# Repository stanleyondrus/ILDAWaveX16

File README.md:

# ILDAWaveX16 - Open Source Laser DAC

**ILDAWaveX16** is an open-source, high-resolution, wireless laser DAC with SD-card playback, network control, and ILDA output.

Traditional laser DACs are often expensive, proprietary, or limited in flexibility, especially for those who want to experiment with laser systems, build custom projectors, or interface with low-cost driver kits.

The goal of this project is to create the "Arduino of laser DACs" - a flexible, hackable platform for makers and enthusiasts that can serve as a foundation for any DIY laser project, capable of real show control, yet simple enough for beginners and hobbyists to learn from.

Full documentation is available at [stanleyprojects.com](https://stanleyprojects.com/projects/ildawavex16)

## Features
- **ESP32-S3 dual-core MCU** @ 240 MHz with native USB, Wi-Fi, and BLE  
- **16-bit, 8-channel DAC (DAC80508)**  
  - X/Y resolution: 65,536 x 65,536  
  - R/G/B resolution: 281 trillion colors  
  - Intensity resolution: 65,536  
  - 16-bit user-programmable channels USR1/USR2  
- **ILDA DB25 connector** for standard projectors  
- **JST XH connectors** for direct wiring to driver kits
- **USB-C power** (no need for bipolar PSU) or optional ±15V external supply  
- **microSD card slot** for ILDA file playback  
- Compact: 55 x 53 mm  

## Firmware

This repository provides a **starting-point firmware**, which is **open-source** and built on the **Arduino framework**. It serves as a foundation for experimenting, learning, and customizing the board for your own projects.  

Although still in development and likely to contain bugs, it includes basic implementations of:
- Playing `.ild` files directly from the SD card  
- **IDN (ILDA Digital Network)** - standard real-time streaming
- **IWP (ILDAWaveProtocol)** - simple, lightweight UDP streaming
- **Web server interface** to control SD card playback, brightness, scan speed, and Wi-Fi settings

Contributions are welcome! Feel free to share improvements, optimizations, or custom firmware to help the community.

## Repository Contents
- `pcb/` - Schematic, BOM  
- `firmware/ILDAWaveX16` - ESP32-S3 source code (Arduino / PlatformIO)  
- `firmware/Python/iwp-ilda.py` - Python script to open `.ild` files and stream over UDP using IWP  
- `firmware/Python/iwp-gen.ipynb` - Jupyter notebook for generating patterns and streaming them via IWP

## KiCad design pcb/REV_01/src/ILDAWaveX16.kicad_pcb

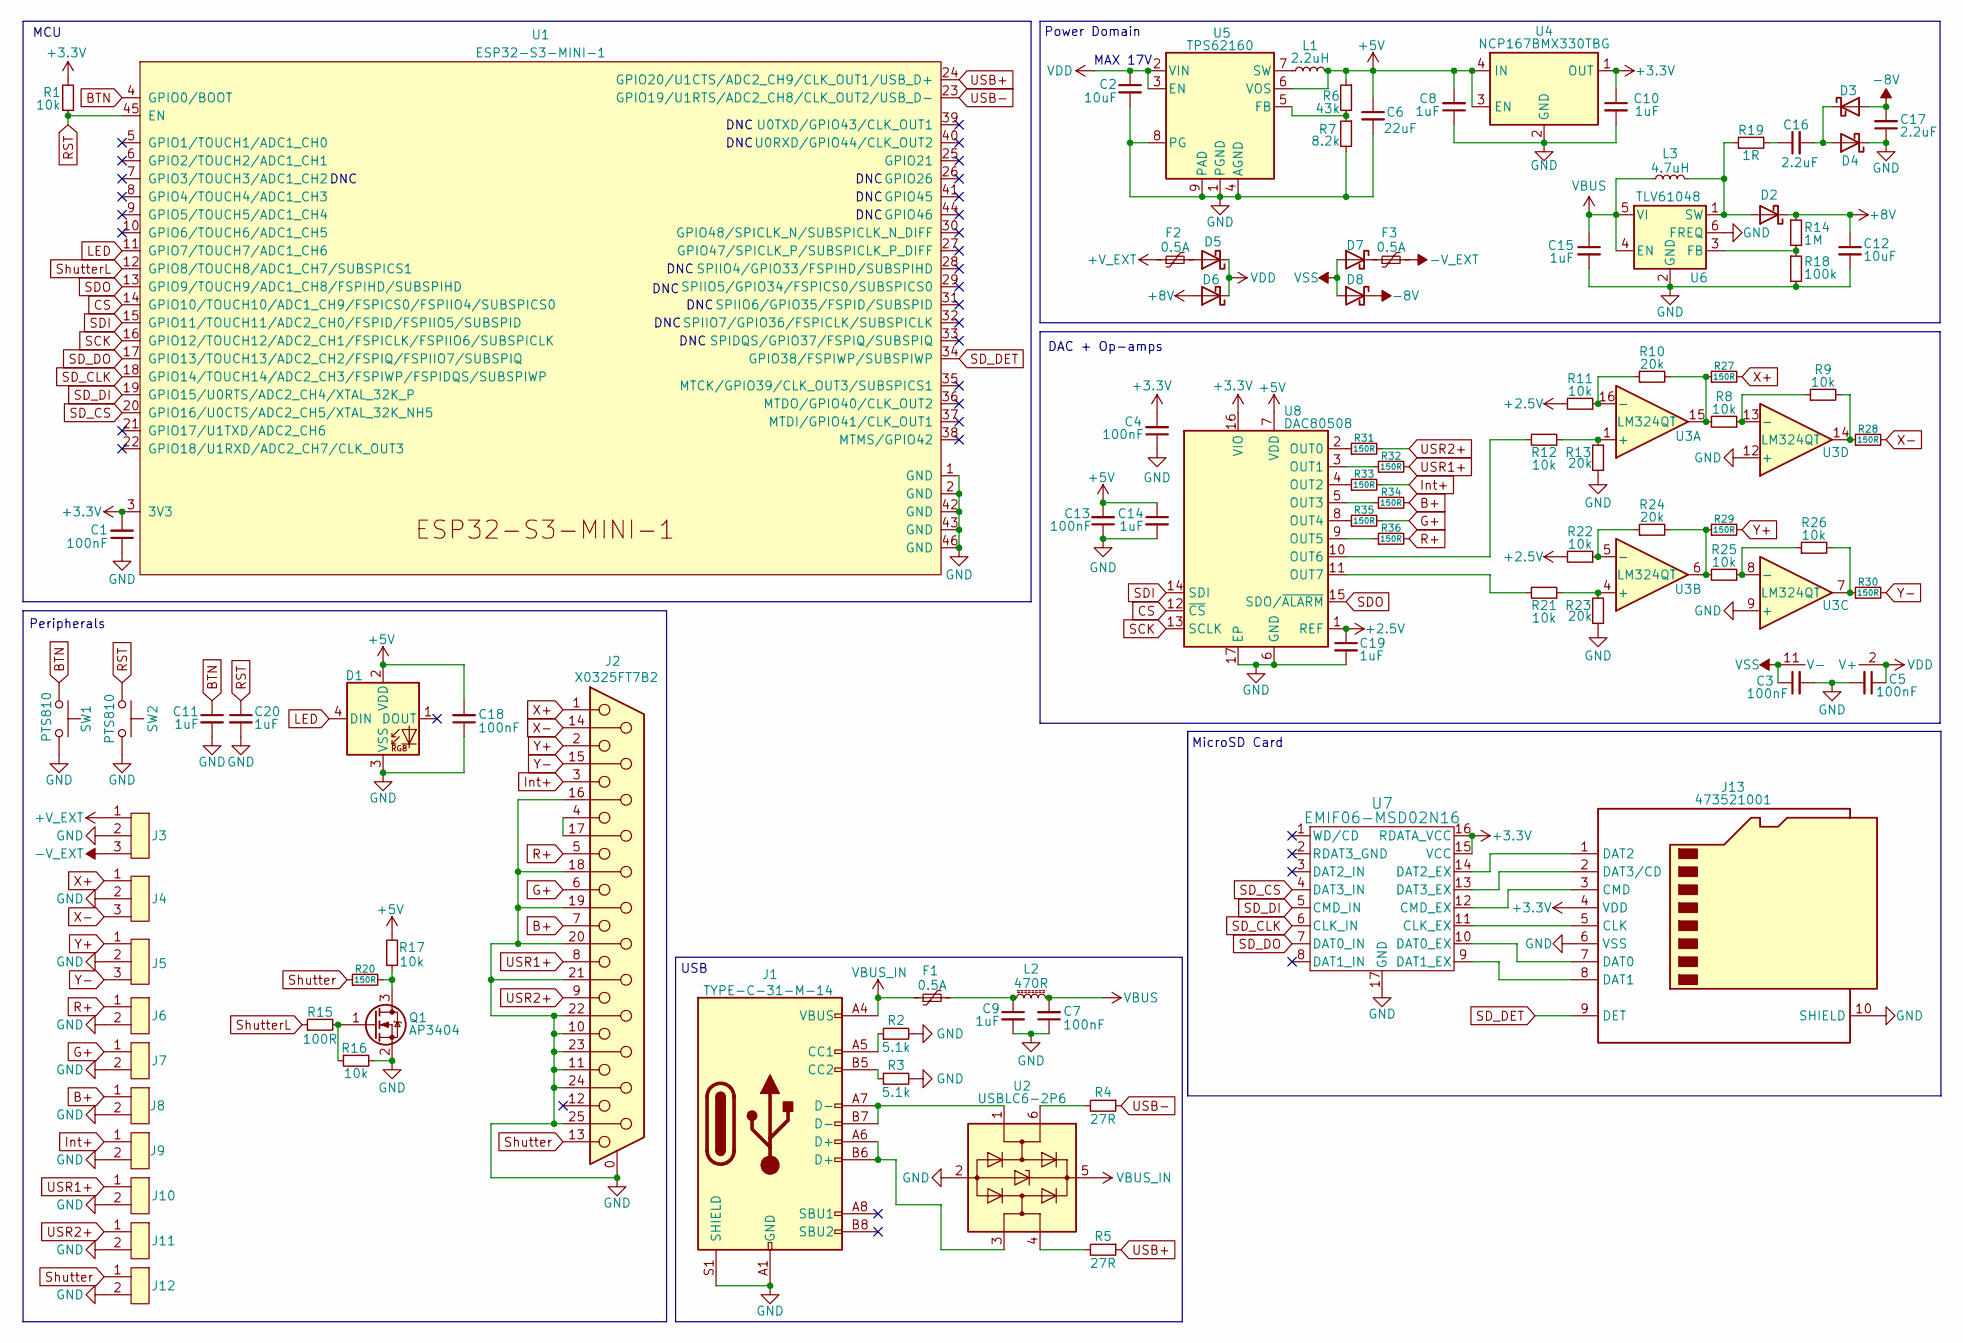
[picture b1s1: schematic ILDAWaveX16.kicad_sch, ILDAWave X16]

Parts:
C1, C3, C4, C5, C7, C13, C18: 100nF; C_0402_1005Metric; MPN CC0402KRX7R7BB104; LCSC# C60474
C2: 10uF; C_0805_2012Metric; MPN CL21A106KAYNNNE; LCSC# C15850
C6: 22uF; C_0805_2012Metric; MPN CL21A226MQQNNNF; LCSC# C307531
C8, C9, C10, C11, C14, C15, C19, C20: 1uF; C_0402_1005Metric; MPN CL05A105KA5NQNC; LCSC# C52923
C12: 10uF; C_1210_3225Metric; MPN CC1206KKX5R8BB106; LCSC# C128855
C16, C17: 2.2uF; C_0603_1608Metric; MPN GRM188R61H225KE11D; LCSC# C162273
D1: XL-1010RGBC-WS2812B; MPN XL-1010RGBC-WS2812B; LCSC# C5349953
D2, D3, D4, D5, D6, D7, D8: 1N5819W; D_SOD-123; MPN 1N5819W; LCSC# C2905650
F1, F2, F3: 0.5A; Fuse_0805_2012Metric; MPN SMD0805-050-16V; LCSC# C2833485
J1: TYPE-C-31-M-14; USB_C_Receptacle_HRO_TYPE-C-31-M-14; MPN TYPE-C-31-M-14; LCSC# C223907
J2: X0325FT7B2; J_DB25_Female_X0325FT7B2; MPN X0325FT7B2; LCSC# C7464461
J3, J4, J5: J_JST-XH-B3B; JST_XH_B3B-XH-A_1x03_P2.50mm_Vertical; MPN B3B-XH-A(LF)(SN); LCSC# C144394
J6, J7, J8, J9, J10, J11, J12: J_JST-XH-B2B; JST_XH_B2B-XH-A_1x02_P2.50mm_Vertical; MPN B2B-XH-A(LF)(SN); LCSC# C158012
J13: 473521001; microSD_HC_Molex_47352-1001; MPN 473521001; LCSC# C293569
L1: 2.2uH; VLCF4020; MPN VLCF4020T-2R2N1R7; LCSC# C136245
L2: 470R; L_0603_1608Metric; MPN MPZ1608B471ATA00; LCSC# C114780
L3: 4.7uH; L_Coilcraft_XAL4030-XXX; MPN XAL4030-472; LCSC# C19191688
Q1: AP3404; SOT-23; MPN AP3404; LCSC# C2842665
R1, R8, R9, R11, R12, R16, R17, R21, R22, R25, R26: 10k; R_0402_1005Metric; MPN RC0402FR-7W10KL; LCSC# C851848
R2, R3: 5.1k; R_0402_1005Metric; MPN AC0402FR-075K1L; LCSC# C144745
R4, R5: 27R; R_0402_1005Metric; MPN RC0402JR-0727RL; LCSC# C137890
R6: 43k; R_0402_1005Metric; MPN RC0402FR-0743KL; LCSC# C185415
R7: 8.2k; R_0402_1005Metric; MPN RC0402FR-078K2L; LCSC# C137929
R10, R13, R23, R24: 20k; R_0402_1005Metric; MPN RC0402FR-0720KL; LCSC# C93942
R14: 1M; R_0402_1005Metric; MPN RK73G1ETTP1004F; LCSC# C516088
R15: 100R; R_0402_1005Metric; MPN AC0402FR-07100RL; LCSC# C144808
R18: 100k; R_0402_1005Metric; MPN 0402WGF1003TCE; LCSC# C25741
R19: 1R; R_0603_1608Metric; MPN HP03W5F100KT5E; LCSC# C2759448
R20, R27, R28, R29, R30, R31, R32, R33, R34, R35, R36: 150R; R_0402_1005Metric; MPN AC0402FR-07150RL; LCSC# C226790
SW1, SW2: PTS810; SW_CK_PTS810; MPN PTS810SJG250SMTRLFS; LCSC# C221895
U1: ESP32-S3-MINI-1; MPN ESP32-S3-MINI-1; LCSC# C2913206
U2: USBLC6-2P6; SOT-666; MPN USBLC6-2P6; LCSC# C15999
U3: LM324QT; QFN-16-1EP_3x3mm_P0.5mm_EP1.7x1.7mm; MPN LM324QT; LCSC# C183029
U4: NCP167BMX330TBG; XDFN-4; MPN NCP167BMX330TBG; LCSC# C892227
U5: TPS62160; WSON-8-1EP_2x2mm_P0.5mm_EP0.9x1.6mm_ThermalVias; MPN TPS62160DSG; LCSC# C324077
U6: TLV61048; SOT-23-6; MPN TLV61048DBV; LCSC# C2861467
U7: EMIF06-MSD02N16; MICROQFN16_1P25X3P55X0P4_STM; MPN EMIF06-MSD02N16; LCSC# C5267594
U8: DAC80508; Texas_RTE0016D_WQFN-16-1EP_3x3mm_P0.5mm_EP0.8x0.8mm_Thermal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; MPN DAC80508MRTE; LCSC# C2679529

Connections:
+2.5V: C19.1, R11.2, R22.2, U8.1 (REF)
+3.3V: C1.2, C4.2, C10.1, J13.4 (VDD), R1.2, U1.3 (3V3), U4.1 (OUT), U7.15 (VCC), U7.16 (RDATA_VCC), U8.16 (VIO)
+5V: C6.1, C8.2, C13.2, C14.1, C18.2, D1.2 (VDD), L1.2, R6.1, R17.2, U4.3 (EN), U4.4 (IN), U5.6 (VOS), U8.7 (VDD)
+8V: C12.1, D2.1 (K), D6.2 (A), R14.1
+V_EXT: F2.1, J3.1
-8V: C17.2, D3.2 (A), D8.1 (K)
-V_EXT: F3.2, J3.3
B+: J2.7, J8.1, R34.2
BTN: C11.1, SW1.1, SW1.2, U1.4 (GPIO0/BOOT)
CS: U1.14 (GPIO10/TOUCH10/ADC1_CH9/FSPICS0/FSPIIO4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), U8.12 (~CS)
G+: J2.6, J7.1, R35.2
GND: C1.1, C2.2, C3.2, C4.1, C5.2, C6.2, C7.1, C8.1, C9.2, C10.2, C11.2, C12.2, C13.1, C14.2, C15.2, C17.1, C18.1, C19.2, C20.2, D1.3 (VSS), D4.1 (K), J1.A1 (GND), J1.A12 (GND), J1.B1 (GND), J1.B12 (GND), J1.S1 (SHIELD), J2.0 (PAD), J2.10, J2.11, J2.16, J2.18, J2.19, J2.20, J2.21, J2.22, J2.23, J2.24, J2.25, J3.2, J4.2, J5.2, J6.2, J7.2, J8.2, J9.2, J10.2, J11.2, J12.2, J13.6 (VSS), J13.10 (SHIELD), Q1.2 (S), R2.2, R3.2, R7.2, R13.1, R16.2, R18.2, R23.1, SW1.3, SW1.4, SW2.3, SW2.4, U1.1 (GND), U1.2 (GND), U1.42 (GND), U1.43 (GND), U1.46 (GND), U2.2 (GND), U3.9 (+), U3.12 (+), U4.2 (GND), U4.5 (GND), U5.1 (PGND), U5.4 (AGND), U5.8 (PG), U5.9 (PAD), U6.2 (GND), U6.6 (FREQ), U7.17 (GND), U8.6 (GND), U8.17 (EP)
Int+: J2.3, J9.1, R33.2
LED: D1.4 (DIN), U1.11 (GPIO7/TOUCH7/ADC1_CH6)
unnamed: C9.1, F1.2, L2.1
unnamed: C16.1, R19.2
unnamed: D2.2 (A), L3.1, R19.1, U6.1 (SW)
unnamed: C16.2, D3.1 (K), D4.2 (A)
unnamed: D5.2 (A), F2.2
unnamed: D7.1 (K), F3.1
unnamed: J1.A5 (CC1), R2.1
unnamed: J1.B5 (CC2), R3.1
unnamed: J1.A6 (D+), J1.B6 (D+), U2.3 (I/O2)
unnamed: J1.A7 (D-), J1.B7 (D-), U2.1 (I/O1)
unnamed: J2.4, J2.17
unnamed: J13.5 (CLK), U7.11 (CLK_EX)
unnamed: J13.3 (CMD), U7.12 (CMD_EX)
unnamed: J13.7 (DAT0), U7.10 (DAT0_EX)
unnamed: J13.8 (DAT1), U7.9 (DAT1_EX)
unnamed: J13.1 (DAT2), U7.14 (DAT2_EX)
unnamed: J13.2 (DAT3/CD), U7.13 (DAT3_EX)
unnamed: Q1.3 (D), R17.1, R20.2
unnamed: Q1.1 (G), R15.2, R16.1
unnamed: R4.2, U2.6 (I/O1)
unnamed: R5.2, U2.4 (I/O2)
unnamed: R8.2, R10.2, R27.1, U3.15
unnamed: R24.2, R25.2, R29.1, U3.6
unnamed: R26.2, R30.1, U3.7
unnamed: R9.2, R28.1, U3.14
unnamed: R12.1, R13.2, U3.1 (+)
unnamed: R10.1, R11.1, U3.16 (-)
unnamed: R21.1, R23.2, U3.4 (+)
unnamed: R22.1, R24.1, U3.5 (-)
unnamed: R25.1, R26.1, U3.8 (-)
unnamed: R8.1, R9.1, U3.13 (-)
unnamed: R6.2, R7.1, U5.5 (FB)
unnamed: L1.1, U5.7 (SW)
unnamed: R14.2, R18.1, U6.3 (FB)
unnamed: R31.1, U8.2 (OUT0)
unnamed: R32.1, U8.3 (OUT1)
unnamed: R33.1, U8.4 (OUT2)
unnamed: R34.1, U8.5 (OUT3)
unnamed: R35.1, U8.8 (OUT4)
unnamed: R36.1, U8.9 (OUT5)
unnamed: R12.2, U8.10 (OUT6)
unnamed: R21.2, U8.11 (OUT7)
R+: J2.5, J6.1, R36.2
RST: C20.1, R1.1, SW2.1, SW2.2, U1.45 (EN)
SCK: U1.16 (GPIO12/TOUCH12/ADC2_CH1/FSPICLK/FSPIIO6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), U8.13 (SCLK)
SDI: U1.15 (GPIO11/TOUCH11/ADC2_CH0/FSPID/FSPIIO5/S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), U8.14 (SDI)
SDO: U1.13 (GPIO9/TOUCH9/ADC1_CH8/FSPIHD/SUBSPIHD), U8.15 (SDO/~ALARM)
SD_CLK: U1.18 (GPIO14/TOUCH14/ADC2_CH3/FSPIWP/FSPIDQS/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), U7.6 (CLK_IN)
SD_CS: U1.20 (GPIO16/U0CTS/ADC2_CH5/XTAL_32K_NH5), U7.4 (DAT3_IN)
SD_DET: J13.9 (DET), U1.34 (GPIO38/FSPIWP/SUBSPIWP)
SD_DI: U1.19 (GPIO15/U0RTS/ADC2_CH4/XTAL_32K_P), U7.5 (CMD_IN)
SD_DO: U1.17 (GPIO13/TOUCH13/ADC2_CH2/FSPIQ/FSPIIO7/S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), U7.7 (DAT0_IN)
Shutter: J2.13, J12.1, R20.1
ShutterL: R15.1, U1.12 (GPIO8/TOUCH8/ADC1_CH7/SUBSPICS1)
USB+: R5.1, U1.24 (GPIO20/U1CTS/ADC2_CH9/CLK_OUT1/USB_D+)
USB-: R4.1, U1.23 (GPIO19/U1RTS/ADC2_CH8/CLK_OUT2/USB_D-)
USR1+: J2.8, J10.1, R32.2
USR2+: J2.9, J11.1, R31.2
VBUS: C7.2, C15.1, L2.2, L3.2, U6.4 (EN), U6.5 (VI)
VBUS_IN: F1.1, J1.A4 (VBUS), J1.A9 (VBUS), J1.B4 (VBUS), J1.B9 (VBUS), U2.5 (VBUS)
VDD: C2.1, C5.1, D5.1 (K), D6.1 (K), U3.2 (V+), U5.2 (VIN), U5.3 (EN)
VSS: C3.1, D7.2 (A), D8.2 (A), U3.11 (V-)
X+: J2.1, J4.1, R27.2
X-: J2.14, J4.3, R28.2
Y+: J2.2, J5.1, R29.2
Y-: J2.15, J5.3, R30.2

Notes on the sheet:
USB
DNC
MAX 17V
MCU
MicroSD Card
Power Domain
Peripherals
DAC + Op-amps

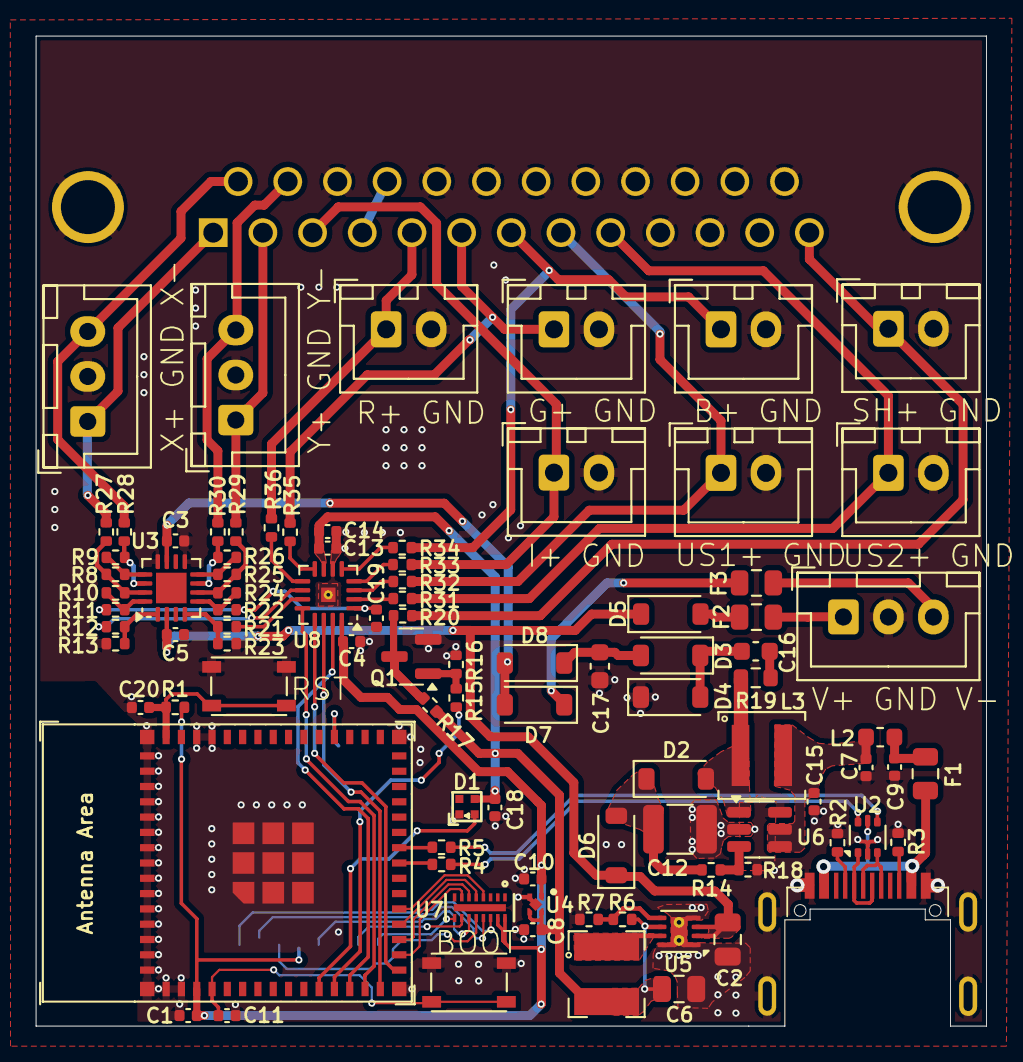
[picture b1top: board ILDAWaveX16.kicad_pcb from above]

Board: 2 copper layers, 52.8 x 55.0 mm, 94 parts (1 on the bottom side), 80 nets.

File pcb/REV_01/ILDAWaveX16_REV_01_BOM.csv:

"Designator","Qty","MPN","Comment","Manufacturer","Footprint","Datasheet","JLCPCB Part #"
"U8","1","DAC80508MRTE","DAC80508","Texas Instruments","WQFN","https://www.ti.com/lit/ds/symlink/dac80508.pdf","C2679529"
"U7","1","EMIF06-MSD02N16","EMIF06-MSD02N16","STMicroelectronics","Micro QFN 3.5x1.2-16L","https://www.st.com/resource/en/datasheet/emif06-msd02n16.pdf","C5267594"
"U6","1","TLV61048DBV","TLV61048","Texas Instruments","SOT-23-6","https://www.ti.com/lit/ds/symlink/tlv61048.pdf","C2861467"
"U5","1","TPS62160DSG","TPS62160","Texas Instruments","WSON-8 (2x2mm)","https://datasheet.lcsc.com/lcsc/1806070425_Texas-Instruments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","C324077"
"U4","1","NCP167BMX330TBG","NCP167BMX330TBG","onsemi","XDFN-4","https://datasheet.lcsc.com/lcsc/2107280040_onsemi-NCP167BMX3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","C892227"
"U3","1","LM324QT","LM324QT","STMicroelectronics","QFN16 3x3","https://www.lcsc.com/datasheet/lcsc_datasheet_1810010620_STM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","C183029"
"U2","1","USBLC6-2P6","USBLC6-2P6","STMicroelectronics","SOT666","https://www.st.com/resource/en/datasheet/usblc6-2.pdf","C15999"
"U1","1","ESP32-S3-MINI-1","ESP32-S3-MINI-1","Espressif Systems","Module","https://www.espressif.com/sites/default/files/documentation/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","C2913206"
"SW1,SW2","2","PTS810SJG250SMTRLFS","PTS810","C&K","3.2x2.5mm SMD","https://datasheet.lcsc.com/lcsc/1810121629_C-K-PTS810SJG250S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","C221895"
"R20,R27,R28,R29,R30,R31,R32,R33,R34,R35,R36","11","AC0402FR-07150RL","150R","Yageo","0402","https://eu.mouser.com/datasheet/2/447/PYu-AC_51_RoHS_L_7-171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","C226790"
"R19","1","HP03W5F100KT5E","1R","UNI-ROYAL","0603","https://www.lcsc.com/datasheet/lcsc_datasheet_2304140030_UNI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","C2759448"
"R18","1","0402WGF1003TCE","100k","UNI-ROYAL(Uniroyal Elec)","0402","https://datasheet.lcsc.com/szlcsc/1810111814_UNI-ROYAL-Uniro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","C25741"
"R15","1","AC0402FR-07100RL","100R","Yageo","0402","https://eu.mouser.com/datasheet/2/447/PYu-AC_51_RoHS_L_7-171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","C144808"
"R14","1","RK73G1ETTP1004F","1M","KOA Speer Elec","0402","https://datasheet.lcsc.com/szlcsc/2004171812_KOA-Speer-Elec-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","C516088"
"R10,R13,R23,R24","4","RC0402FR-0720KL","20k","YAGEO","0402","https://www.lcsc.com/datasheet/lcsc_datasheet_2304140030_YAG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","C93942"
"R7","1","RC0402FR-078K2L","8.2k","Yageo","0402","https://www.lcsc.com/datasheet/lcsc_datasheet_2304140030_YAG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","C137929"
"R6","1","RC0402FR-0743KL","43k","Yageo","0402","https://www.lcsc.com/datasheet/lcsc_datasheet_2304140030_YAG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","C185415"
"R4,R5","2","RC0402JR-0727RL","27R","YAGEO","0402","https://datasheet.lcsc.com/szlcsc/1810241322_YAGEO-RC0402JR-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","C137890"
"R2,R3","2","AC0402FR-075K1L","5.1k","YAGEO","0402","https://datasheet.lcsc.com/szlcsc/1810241326_YAGEO-AC0402FR-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","C144745"
"R1,R8,R9,R11,R12,R16,R17,R21,R22,R25,R26","11","RC0402FR-7W10KL","10k","YAGEO","0402","https://datasheet.lcsc.com/lcsc/2104091834_YAGEO-RC0402FR-7W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","C851848"
"Q1","1","AP3404","AP3404","ALLPOWER(ShenZhen Quan Li Semiconductor)","SOT-23","https://datasheet.lcsc.com/lcsc/2202132030_ALLPOWER-ShenZhen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","C2842665"
"L3","1","XAL4030-472","4.7uH","Coilcraft","4.0x4.0x3.1","https://www.coilcraft.com/getmedia/6adcb47d-8b55-416c-976e-1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","C19191688"
"L2","1","MPZ1608B471ATA00","470R","TDK","0603","https://www.lcsc.com/datasheet/lcsc_datasheet_1811131653_TDK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","C114780"
"L1","1","VLCF4020T-2R2N1R7","2.2uH","TDK","4x4x2mm","https://datasheet.lcsc.com/szlcsc/1810211523_TDK-VLCF4020T-2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","C136245"
"J13","1","473521001","473521001","Molex","SMD","https://www.molex.com/content/dam/molex/molex-dot-com/produc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","C293569"
"J6,J7,J8,J9,J10,J11,J12","7","B2B-XH-A(LF)(SN)","J_JST-XH-B2B","JST Sales America","Through Hole, P=2.5mm","http://www.jst-mfg.com/product/pdf/eng/eXH.pdf","C158012"
"J3,J4,J5","3","B3B-XH-A(LF)(SN)","J_JST-XH-B3B","JST Sales America","Through Hole, P=2.5mm","http://www.jst-mfg.com/product/pdf/eng/eXH.pdf","C144394"
"J2","1","X0325FT7B2","X0325FT7B2","XKB Connection","25P","https://www.lcsc.com/datasheet/lcsc_datasheet_2307171038_XKB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","C7464461"
"J1","1","TYPE-C-31-M-14","TYPE-C-31-M-14","Korean Hroparts Elec","16pin USB C","https://www.usb.org/sites/default/files/documents/usb_type-c.zip","C223907"
"F1,F2,F3","3","SMD0805-050-16V","0.5A","TECHFUSE","0805","https://www.lcsc.com/datasheet/lcsc_datasheet_2105241447_TEC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","C2833485"
"D2,D3,D4,D5,D6,D7,D8","7","1N5819W","1N5819W","TECH PUBLIC","SOD-123","https://datasheet.lcsc.com/lcsc/2110200930_TECH-PUBLIC-1N581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","C2905650"
"D1","1","XL-1010RGBC-WS2812B","XL-1010RGBC-WS2812B","XINGLIGHT","1010 (1x1mm)","https://datasheet.lcsc.com/lcsc/2301111010_XINGLIGHT-XL-1010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","C5349953"
"C16,C17","2","GRM188R61H225KE11D","2.2uF","Murata Electronics","0603","https://datasheet.lcsc.com/lcsc/1912111437_Murata-Electronic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","C162273"
"C12","1","CC1206KKX5R8BB106","10uF","YAGEO","1210","https://www.lcsc.com/datasheet/lcsc_datasheet_2407081117_YAG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","C128855"
"C8,C9,C10,C11,C14,C15,C19,C20","8","CL05A105KA5NQNC","1uF","Samsung Electro-Mechanics","0402","https://datasheet.lcsc.com/szlcsc/1811091611_Samsung-Electro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","C52923"
"C6","1","CL21A226MQQNNNF","22uF","Samsung Electro-Mechanics","0805","https://datasheet.lcsc.com/lcsc/2304140030_Samsung-Electro-M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","C307531"
"C2","1","CL21A106KAYNNNE","10uF","Samsung Electro-Mechanics","0805","https://datasheet.lcsc.com/szlcsc/1811121310_Samsung-Electro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","C15850"
"C1,C3,C4,C5,C7,C13,C18","7","CC0402KRX7R7BB104","100nF","Yageo","0402","https://www.yageo.com/upload/media/product/productsearch/dat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","C60474"

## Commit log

2025-11-20 init
2025-12-05 Update README - correct JST connectors
2025-12-14 Add KiCad source project
2026-01-24 configuration for N8 and N4R2 version
2026-01-26 redesigned HTML website to be dark and responsive.
    redesign ESP32 interface with responsive dark theme
    - Modern card-based layout with CSS variables
    - Mobile-friendly responsive design
    - Animated rainbow header
    - Minified assets.
    - added footer link to stanleyprojects.com
